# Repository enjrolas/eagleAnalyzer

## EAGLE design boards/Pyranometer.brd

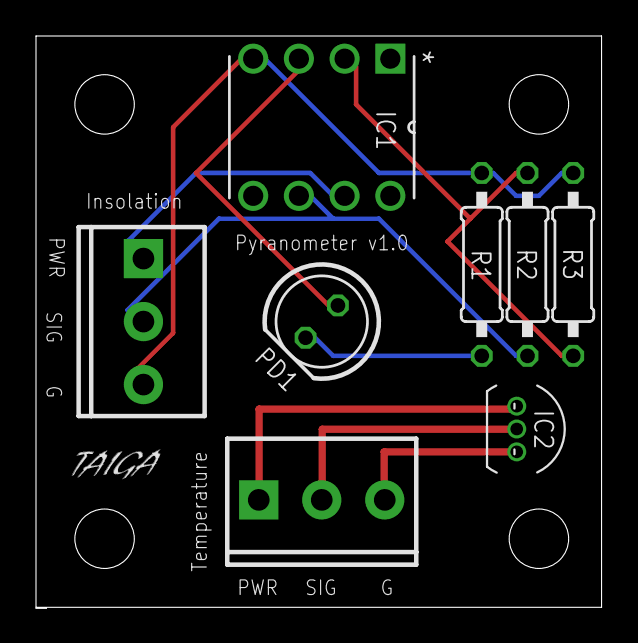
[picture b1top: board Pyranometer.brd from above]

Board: 2 copper layers, 31.4 x 31.7 mm, 12 parts (0 on the bottom side), 9 nets.

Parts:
IC1: LTC1050CN8PBF; DIP254P762X508-8
IC2: LM35; TO92-OVAL
JP1, JP2, JP3, JP4: STAND-OFF
PD1: LED5MM
R1, R2, R3: 0207/10
U$1, U$2: SCREWTERM3-3P5; SCREWTERM3P5-3

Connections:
5V: IC1.7, U$1.P1-1
GND: IC1.4, R1.2, R3.2, U$1.P1-3
unnamed: PD1.K, R1.1
unnamed: IC1.3, PD1.A
unnamed: IC1.2, R2.1, R3.1
unnamed: IC2.1, U$2.P1-1
unnamed: IC2.3, U$2.P1-3
unnamed: IC2.2, U$2.P1-2
SIG: IC1.6, R2.2, U$1.P1-2

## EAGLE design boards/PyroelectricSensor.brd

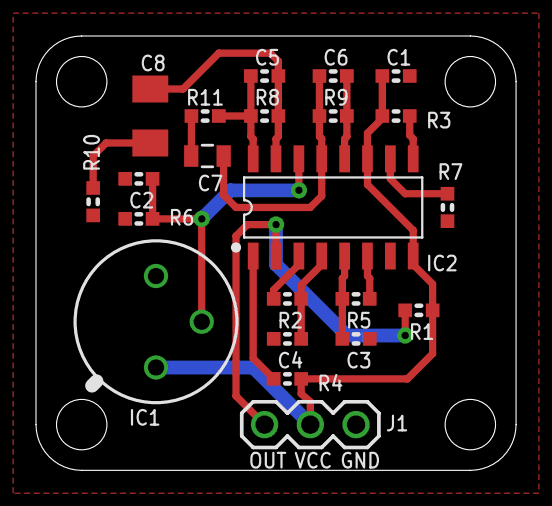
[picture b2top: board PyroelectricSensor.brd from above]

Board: 2 copper layers, 26.7 x 24.1 mm, 23 parts (1 on the bottom side), 17 nets.

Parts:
C1: 100nF; 0603
C2, C3, C4, C5, C6: 10nF; 0603
C7: 10µF; 0805
C8: 47µF; C1206K
IC1: RE200B; TO5-CAN
IC2: BIS0001; 16-SOIC
J1: 1X03
R1, R2, R3, R4, R11: 10kΩ; 0603
R5: 15kΩ; 0603
R6, R10: 47kΩ; 0603
R7, R9: 1MΩ; 0603
R8: 2MΩ; 0603
SY: OSHW-LOGOS; OSHW-LOGO-S

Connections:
+3V3: C1.1, IC1.1, IC2.8, IC2.11, J1.2, R1.2, R3.2, R4.2
GND: C1.2, C2.2, C3.2, C4.2, IC1.3, IC2.7, J1.3, R6.1, R7.1, R10.2
unnamed: IC2.6, R5.2
unnamed: IC2.10, R7.2
unnamed: C5.1, C8.2, IC2.15, R8.2
unnamed: IC2.2, J1.1, R1.1
unnamed: IC2.1, R4.1
unnamed: IC2.3, R2.2
unnamed: C4.1, IC2.4, R2.1
unnamed: C3.1, IC2.5, R5.1
unnamed: IC2.9, R3.1
unnamed: C2.1, IC1.2, IC2.14, R6.2
unnamed: C6.1, C7.2, IC2.13, R9.2
unnamed: C6.2, IC2.12, R9.1
unnamed: C5.2, IC2.16, R8.1, R11.2
unnamed: C7.1, R11.1
unnamed: C8.1, R10.1

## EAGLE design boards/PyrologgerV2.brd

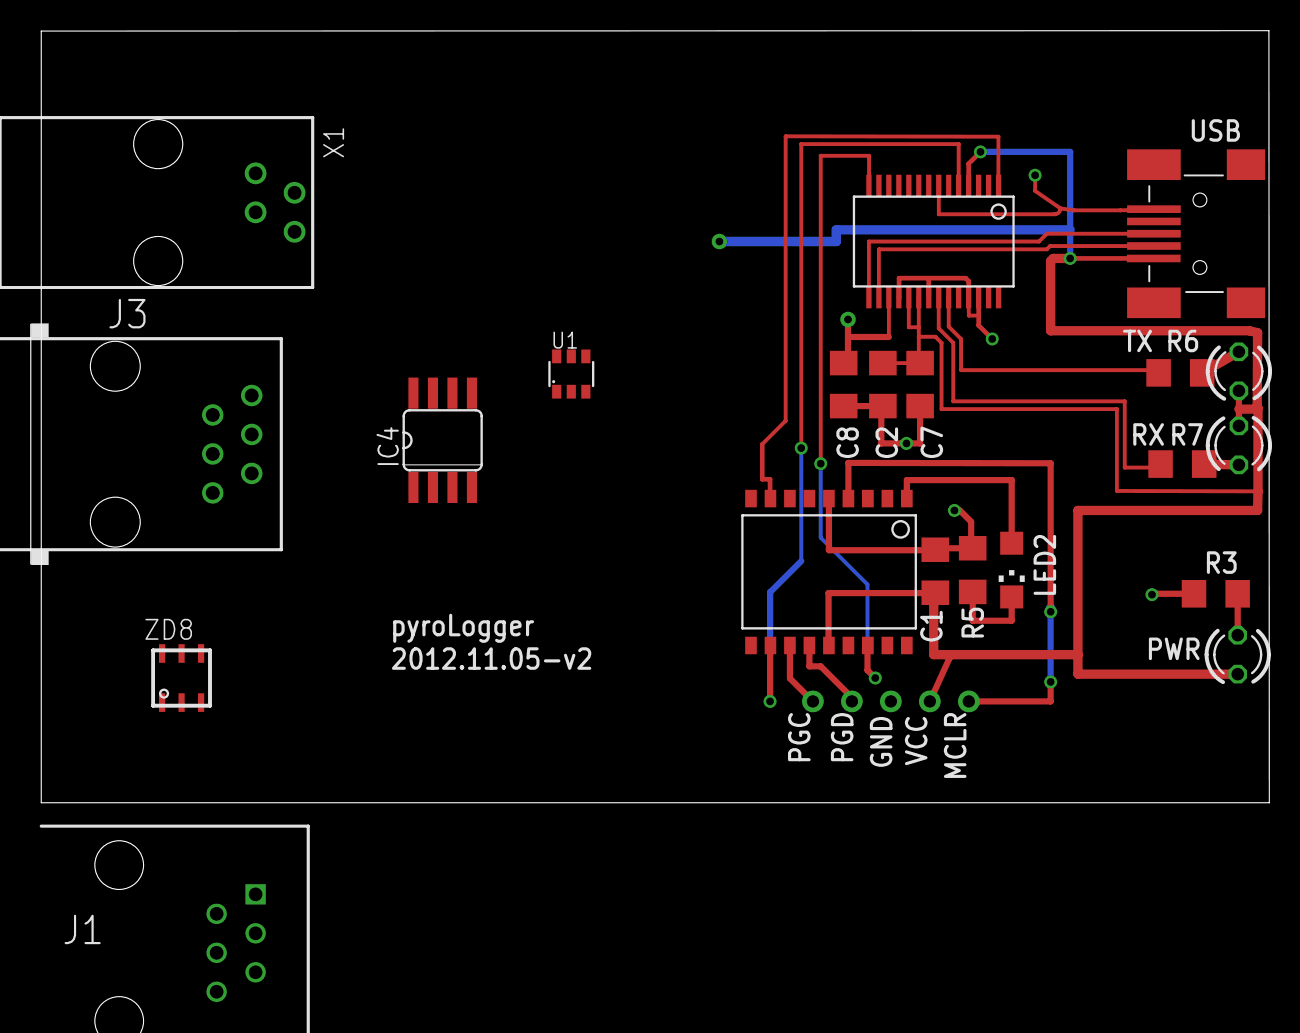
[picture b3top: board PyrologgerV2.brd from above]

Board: 2 copper layers, 80.7 x 50.3 mm, 26 parts (0 on the bottom side), 18 nets.

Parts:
C1, C8: .1uF; C1206@1
C2: 4.7uF; C1206@1
C7: .01uF; C1206@1
IC1: 16F88; SO-18W
IC2: FT232RL; SSOP28DB
IC4: DS2482-100S; SO08
J1: CONN-RJ11
J3: RJ11-2L-B; RJ11-NO_SHIELD
LED1, LED3, LED4: LED3MM
LED2: CHIPLED_1206
R3, R5, R6, R7: 330; R1206
TP1, TP2, TP5, TP6, TP7: PTR1PAD1-13; P1-13@1
U1: DS2483; TSOT23
X1: 14867
X4: USBMINIB; USB-MINIB
ZD8: DS9503P; TSOC6

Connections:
3.3V: C8.1, IC2.17
+5V: C1.1, C2.1, C7.1, IC1.14, IC2.4, IC2.19, IC2.20, LED1.A, LED3.A, LED4.A, TP6.TP, X4.VBUS
GND: C1.2, C2.2, C7.2, C8.2, IC1.5, IC2.7, IC2.18, IC2.21, IC2.25, IC2.26, IC4.3, J1.5, R3.1, R5.2, TP5.TP, U1.4, X4.GND
MCLR: IC1.4, TP7.TP
unnamed: IC2.15, X4.D+
unnamed: IC2.16, X4.D-
unnamed: LED3.K, R6.2
unnamed: LED4.K, R7.2
unnamed: IC2.23, R6.1
unnamed: IC2.22, R7.1
unnamed: LED1.K, R3.2
unnamed: IC1.1, LED2.A
unnamed: LED2.C, R5.1
OSC: IC1.16, IC2.14
PGC: IC1.13, TP1.TP
PGD: IC1.12, TP2.TP
RX: IC1.8, IC2.1
TX: IC1.11, IC2.5

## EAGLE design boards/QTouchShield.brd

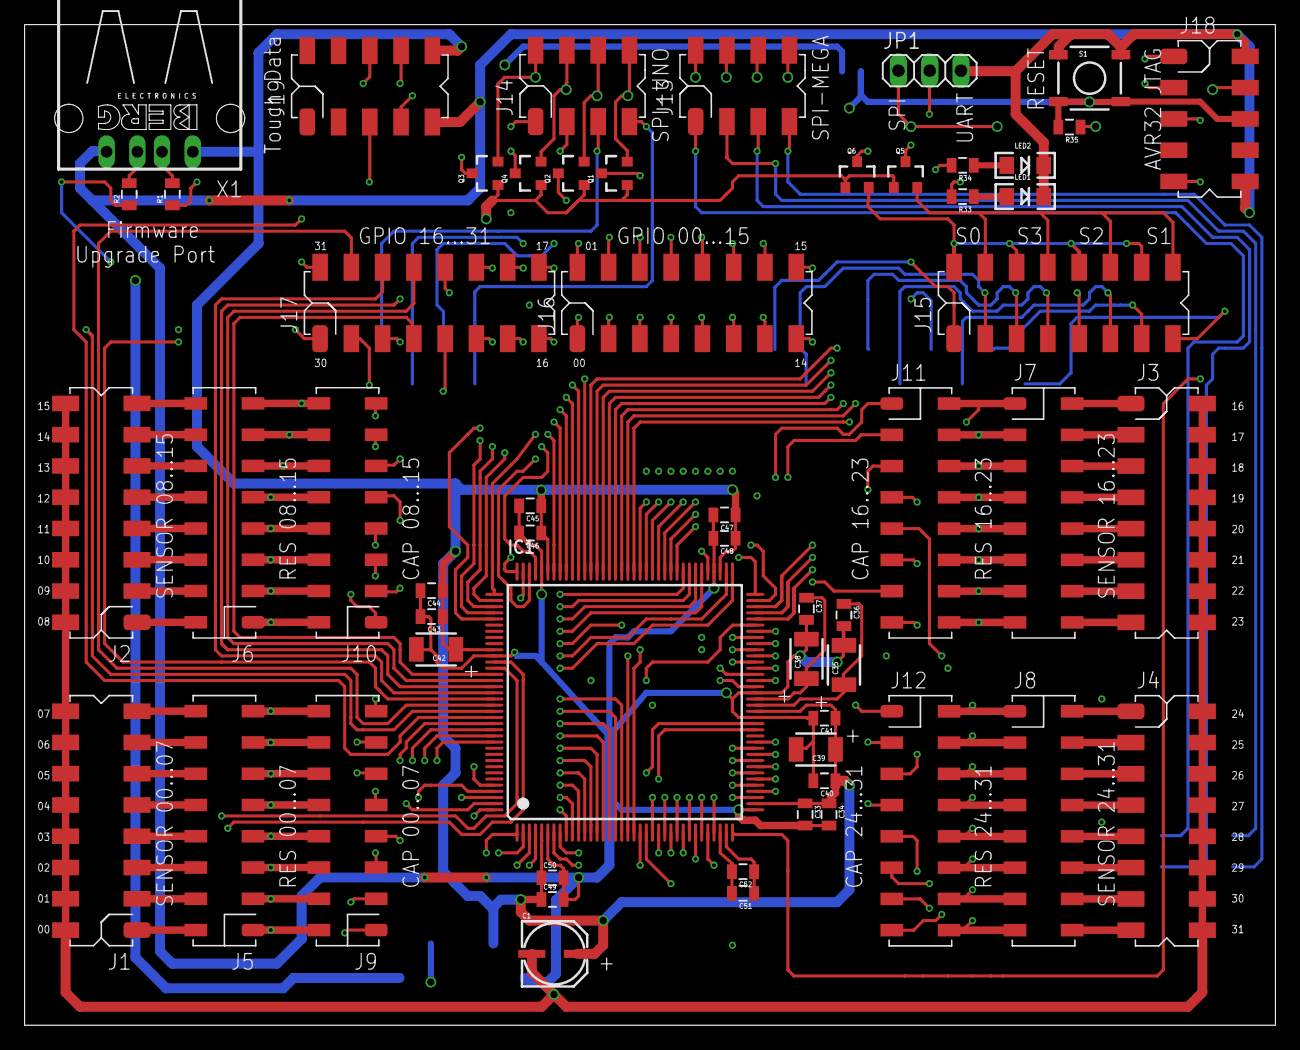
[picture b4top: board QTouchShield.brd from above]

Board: 4 copper layers, 101.6 x 81.3 mm, 59 parts (1 on the bottom side), 182 nets.

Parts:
C1: 10uF/35V; PANASONIC_C
C33, C40, C43, C45, C47, C49, C51: 100nF; 0805
C34, C41, C44, C46, C48, C50, C52: 33nF; 0805
C35, C38: 2.2uF; 1210
C36, C37: 470pF; 0805
C39, C42: 4.7uF; 1210
IC1: AT32UC3C0512CJEDEC-MS-026; LQFP144
J1: SENSOR 00...07; 2X8-V-MALE-SMT-HARWIN
J2: SENSOR 08...15; 2X8-V-MALE-SMT-HARWIN
J3: SENSOR 16...23; 2X8-V-MALE-SMT-HARWIN
J4: SENSOR 24...31; 2X8-V-MALE-SMT-HARWIN
J5: RES 00...07; 2X8-V-FEMALE-SMT-HARWIN
J6: RES 08...15; 2X8-V-FEMALE-SMT-HARWIN
J7: RES 16...23; 2X8-V-FEMALE-SMT-HARWIN
J8: RES 24...31; 2X8-V-FEMALE-SMT-HARWIN
J9: CAP 00...07; 2X8-V-FEMALE-SMT-HARWIN
J10: CAP 08...15; 2X8-V-FEMALE-SMT-HARWIN
J11: CAP 16...23; 2X8-V-FEMALE-SMT-HARWIN
J12: CAP 24...31; 2X8-V-FEMALE-SMT-HARWIN
J13: SPI-MEGA; 2X4-V-MALE-SMT-HARWIN
J14: SPI-UNO; 2X4-V-MALE-SMT-HARWIN
J15: COMMS Select; 2X8-V-MALE-SMT-HARWIN
J16: DETECT00...15; 2X8-V-MALE-SMT-HARWIN
J17: DETECT16...31; 2X8-V-MALE-SMT-HARWIN
J18: JTAG; 2X5-V-MALE-SMT-HARWIN
J19: TOUCH DATA; 2X5-V-MALE-SMT-HARWIN
JP1: COMMS_SELECT; 1X03
LED1: Yellow; LED-1206
LED2: Green; LED-1206
Q1, Q2, Q3, Q4, Q5, Q6: BSS138; SOT23-3
R1, R2: 39R; 0805
R33, R34: 470Ohm; 0805
R35: 10K; 0805
S1: RESET; TACTILE_SWITCH_SMD
SJ5: RESET-LINK; SJ
U1: ARDUINO-2560-MEGA-R3-SMD; ARDUINO-2560-R3-SMD
X1: Firmware Upgrade Port; PN87520

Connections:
ADCVREFN: C51.1, C52.1, IC1.35
ADCVREFP: C51.2, C52.2, IC1.34
ADT-SPI0-MISO: J13.2, J14.2, Q3.2
ADT-SPI0-MOSI: J13.4, J14.4, Q4.2
ADT-SPI0-SCK: J13.6, J14.6, Q2.2
ADT-SPI0-SS: J13.8, J14.8, Q1.2
ADT-USART0-RXD: J15.4, J15.8, J15.12, J15.16, Q5.2
ADT-USART0-TXD: J15.2, J15.6, J15.10, J15.14, Q6.2
ARDUINO_RESET: SJ5.1, U1.RESET
GND: C1.-, C33.2, C34.2, C35.2, C36.2, C37.2, C38.2, C39.2, C40.2, C41.2, C42.2, C43.2, C44.2, C45.2, C46.2, C47.2, C48.2, C49.2, C50.2, IC1.6, IC1.37, IC1.52, IC1.56, IC1.76, IC1.104, IC1.119, J1.2, J1.4, J1.6, J1.8, J1.10, J1.12, J1.14, J1.16, J2.2, J2.4, J2.6, J2.8, J2.10, J2.12, J2.14, J2.16, J3.2, J3.4, J3.6, J3.8, J3.10, J3.12, J3.14, J3.16, J4.2, J4.4, J4.6, J4.8, J4.10, J4.12, J4.14, J4.16, J18.2, J18.10, J19.9, JP1.3, LED1.C, LED2.C, S1.1, S1.2, U1.GND_1, U1.GND_2, X1.4
IOREF: Q1.1, Q2.1, Q3.1, Q4.1, Q5.1, Q6.1, U1.IOREF
JTAG_RESET: IC1.142, J18.6, R35.2, S1.3, S1.4, SJ5.2
JTAG_TCK: IC1.1, J18.1
JTAG_TDI: IC1.2, J18.9
JTAG_TDO: IC1.3, J18.3
JTAG_TMS: IC1.4, J18.5
MISO-MEGA: J13.1, U1.50
MISO-UNO: J14.1, U1.PWM12
MOSI-MEGA: J13.3, U1.51
MOSI-UNO: J14.3, U1.PWM11
unnamed: LED1.A, R33.1
unnamed: J4.15, J8.16
unnamed: J4.13, J8.14
unnamed: J4.11, J8.12
unnamed: J4.9, J8.10
unnamed: J4.7, J8.8
unnamed: J4.5, J8.6
unnamed: J4.3, J8.4
unnamed: J4.1, J8.2
unnamed: J3.15, J7.16
unnamed: J3.13, J7.14
unnamed: J3.11, J7.12
unnamed: J3.9, J7.10
unnamed: J3.7, J7.8
unnamed: J3.5, J7.6
unnamed: J3.3, J7.4
unnamed: J3.1, J7.2
unnamed: J2.15, J6.16
unnamed: J2.13, J6.14
unnamed: J2.11, J6.12
unnamed: J2.9, J6.10
unnamed: J2.7, J6.8
unnamed: J2.5, J6.6
unnamed: J2.3, J6.4
unnamed: J2.1, J6.2
unnamed: J1.15, J5.16
unnamed: J1.13, J5.14
unnamed: J1.11, J5.12
unnamed: J1.9, J5.10
unnamed: J1.7, J5.8
unnamed: J1.5, J5.6
unnamed: J1.3, J5.4
unnamed: J1.1, J5.2
unnamed: R1.2, X1.2
unnamed: R2.2, X1.3
unnamed: LED2.A, R34.1
QT-DETECT-GENERAL: IC1.21, R33.2
RX0: J15.3, U1.RX_PWM00
RX1: J15.15, U1.RX1_19
RX2: J15.11, U1.RX2_17
RX3: J15.7, U1.RX3_15
SCK-MEGA: J13.5, U1.52
SCK-UNO: J14.5, U1.PWM13
SDT-SPI0-MISO: IC1.112, Q3.3
SDT-SPI0-MOSI: IC1.111, Q4.3
SDT-SPI0-SCK: IC1.113, Q2.3
SDT-SPI0-SS: IC1.110, Q1.3
SDT-USART0-RXD: IC1.108, Q6.3
SDT-USART0-TXD: IC1.107, Q5.3
SHIELD-DATA-TRANSFER-COM-SELECT: IC1.109, JP1.2
SHIELD-DATA-TRANSFER-VISUAL-OUTPUT: IC1.22, R34.2
SHIELD-DETECT0: IC1.23, J16.1
SHIELD-DETECT1: IC1.24, J16.2
SHIELD-DETECT2: IC1.25, J16.3
SHIELD-DETECT3: IC1.26, J16.4
SHIELD-DETECT4: IC1.27, J16.5
SHIELD-DETECT5: IC1.28, J16.6
SHIELD-DETECT6: IC1.29, J16.7
SHIELD-DETECT7: IC1.30, J16.8
SHIELD-DETECT8: IC1.31, J16.9
SHIELD-DETECT9: IC1.32, J16.10
SHIELD-DETECT10: IC1.33, J16.11
SHIELD-DETECT11: IC1.36, J16.12
SHIELD-DETECT12: IC1.39, J16.13
SHIELD-DETECT13: IC1.40, J16.14
SHIELD-DETECT14: IC1.41, J16.15
SHIELD-DETECT15: IC1.42, J16.16
SHIELD-DETECT16: IC1.43, J17.15
SHIELD-DETECT17: IC1.44, J17.16
SHIELD-DETECT18: IC1.45, J17.13
SHIELD-DETECT19: IC1.46, J17.14
SHIELD-DETECT20: IC1.47, J17.11
SHIELD-DETECT21: IC1.48, J17.12
SHIELD-DETECT22: IC1.120, J17.9
SHIELD-DETECT23: IC1.121, J17.10
SHIELD-DETECT24: IC1.122, J17.7
SHIELD-DETECT25: IC1.123, J17.8
SHIELD-DETECT26: IC1.124, J17.5
SHIELD-DETECT27: IC1.125, J17.6
SHIELD-DETECT28: IC1.126, J17.3
SHIELD-DETECT29: IC1.127, J17.4
SHIELD-DETECT30: IC1.128, J17.1
SHIELD-DETECT31: IC1.129, J17.2
SNS0: IC1.140, J9.1
SNS1: IC1.141, J9.3
SNS2: IC1.143, J9.5
SNS3: IC1.144, J9.7
SNS4: IC1.7, J9.9
SNS5: IC1.8, J9.11
SNS6: IC1.9, J9.13
SNS7: IC1.10, J9.15
SNS8: IC1.11, J10.1
SNS9: IC1.12, J10.3
SNS10: IC1.13, J10.5
SNS11: IC1.14, J10.7
SNS12: IC1.15, J10.9
SNS13: IC1.16, J10.11
SNS14: IC1.17, J10.13
SNS15: IC1.18, J10.15
SNS16: IC1.19, J11.1
SNS17: IC1.20, J11.3
SNS18: IC1.57, J11.5
SNS19: IC1.58, J11.7
SNS20: IC1.59, J11.9
SNS21: IC1.60, J11.11
SNS22: IC1.61, J11.13
SNS23: IC1.62, J11.15
SNS24: IC1.63, J12.1
SNS25: IC1.64, J12.3
SNS26: IC1.65, J12.5
SNS27: IC1.66, J12.7
SNS28: IC1.67, J12.9
SNS29: IC1.68, J12.11
SNS30: IC1.69, J12.13
SNS31: IC1.70, J12.15
SNSK0: IC1.71, J5.1, J9.2
SNSK1: IC1.72, J5.3, J9.4
SNSK2: IC1.73, J5.5, J9.6
SNSK3: IC1.74, J5.7, J9.8
SNSK4: IC1.77, J5.9, J9.10
SNSK5: IC1.78, J5.11, J9.12
SNSK6: IC1.79, J5.13, J9.14
SNSK7: IC1.80, J5.15, J9.16
SNSK8: IC1.81, J6.1, J10.2
SNSK9: IC1.82, J6.3, J10.4
SNSK10: IC1.83, J6.5, J10.6
SNSK11: IC1.84, J6.7, J10.8
SNSK12: IC1.85, J6.9, J10.10
SNSK13: IC1.86, J6.11, J10.12
SNSK14: IC1.87, J6.13, J10.14
SNSK15: IC1.88, J6.15, J10.16
SNSK16: IC1.89, J7.1, J11.2
SNSK17: IC1.90, J7.3, J11.4
SNSK18: IC1.91, J7.5, J11.6
SNSK19: IC1.92, J7.7, J11.8
SNSK20: IC1.93, J7.9, J11.10
SNSK21: IC1.94, J7.11, J11.12
SNSK22: IC1.95, J7.13, J11.14
SNSK23: IC1.96, J7.15, J11.16
SNSK24: IC1.97, J8.1, J12.2
SNSK25: IC1.98, J8.3, J12.4
SNSK26: IC1.99, J8.5, J12.6
SNSK27: IC1.100, J8.7, J12.8
SNSK28: IC1.101, J8.9, J12.10
SNSK29: IC1.102, J8.11, J12.12
SNSK30: IC1.105, J8.13, J12.14
SNSK31: IC1.106, J8.15, J12.16
SS-MEGA: J13.7, U1.53
SS-UNO: J14.7, U1.PWM10
TOUCH_DATA-MISO: IC1.133, J19.7
TOUCH_DATA-MOSI: IC1.132, J19.6
TOUCH_DATA-SCK: IC1.131, J19.8
TOUCH_DATA-SS: IC1.130, J19.5
TX0: J15.1, U1.TX_PWM01
TX1: J15.13, U1.TX1_18
TX2: J15.9, U1.TX2_16
TX3: J15.5, U1.TX3_14
USB-DM: IC1.50, R1.1
USB-DP: IC1.51, R2.1
VCC: C1.+, C33.1, C34.1, C39.1, C40.1, C41.1, C42.1, C43.1, C44.1, C45.1, C46.1, C47.1, C48.1, C49.1, C50.1, IC1.5, IC1.38, IC1.53, IC1.75, IC1.103, IC1.118, J18.4, J19.10, JP1.1, R35.1, U1.5V_1, X1.1
VDDCORE: C37.1, C38.1, IC1.55
VDDIN_33: C35.1, C36.1, IC1.54

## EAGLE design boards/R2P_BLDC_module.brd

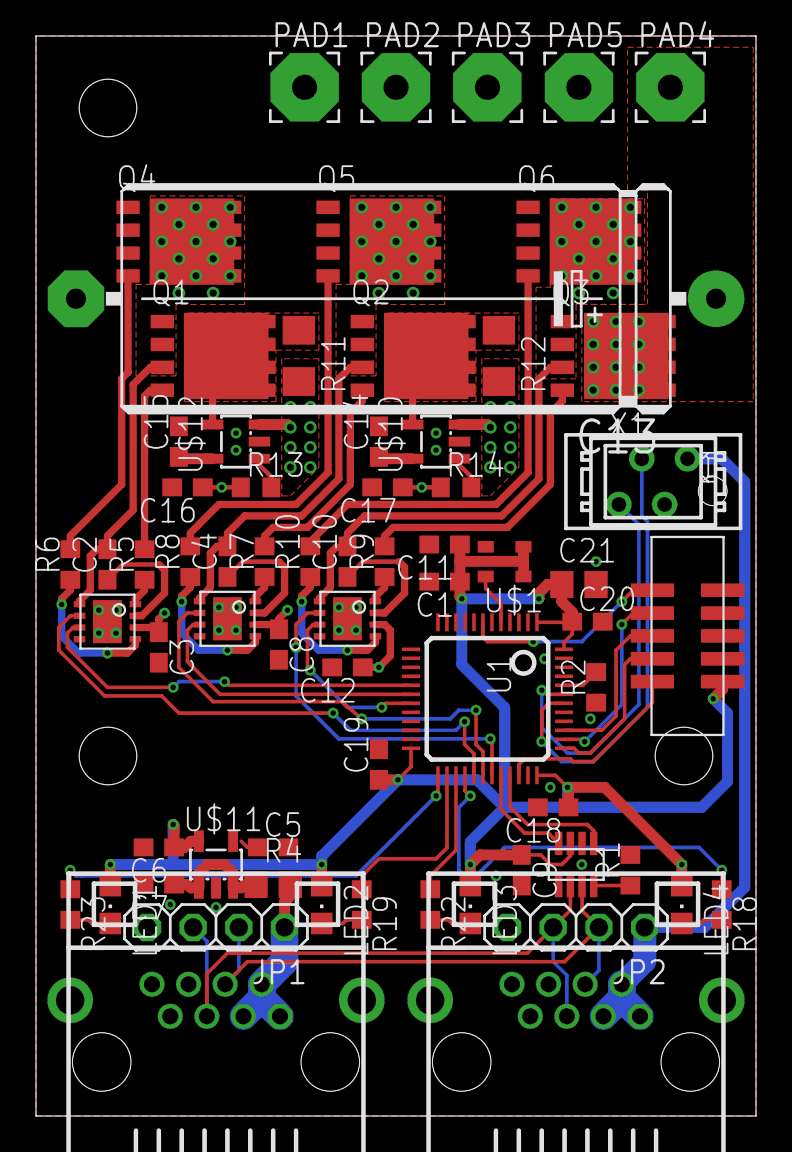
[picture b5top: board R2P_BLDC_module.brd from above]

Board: 2 copper layers, 40.0 x 60.0 mm, 68 parts (0 on the bottom side), 59 nets.

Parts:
1, 2: RJ45-43860; 0438600010
C1, C9, C14, C15, C16, C17, C18, C19, C20: 100n; C0603
C2, C4, C10, C11: 15pF; C0603
C3, C8, C12: 470nF; C0603
C5: 10n; C0603
C6, C7: 1u; C0603
C13: E35-12
C21: 4.7u; C0805
JP1, JP2: 1X04
LED1, LED2, LED3, LED4: CHIPLED_0805
PAD1, PAD2, PAD3, PAD4, PAD5: 3,81/1,4
Q1, Q2, Q3, Q4, Q5, Q6: OPTIMOS; PG-TDSON-8
R1: 0; R0603
R2: 10k; R0603
R4: PTC; R0805
R5, R6, R7, R8, R9, R10, R13, R14: 10; R0603
R11, R12: R1206
R18, R19, R22, R23: 330; R0603
SOT1: MAX3051; SOT23-8L
U1: STM32F103CX; LQFP48
U$1: ASE
U$2, U$8, U$9: MCP14700MF; DFN8
U$4: FTSH-105
U$10, U$12: INA193DBV; SOT23-5L
U$11: TPS73033; SOT23-5L
X1: MICROMATCH-4

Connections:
+3V3: C1.1, C6.1, C9.1, C11.1, C18.1, C19.1, C20.1, C21.1, LED1.A, LED2.A, LED3.A, LED4.A, SOT1.P$3, U1.1, U1.24, U1.36, U1.48, U$1.1, U$1.4, U$4.P$1, U$11.5
+5V: C3.1, C7.1, C8.1, C12.1, R4.1, U$2.P$6, U$8.P$6, U$9.P$6, U$11.1, U$11.3
+A3V3: C14.1, C15.1, U1.9, U$10.5, U$12.5
+V: C13.+, PAD4.1, Q3.5, Q3.6, Q3.7, Q3.8, Q3.TH, R11.2, R12.2, U$10.3, U$12.3
+VBUS: 1.P$1, 1.P$2, 1.P$3, 2.P$1, 2.P$2, 2.P$3, JP1.1, JP2.1, R4.2, X1.1
AH: U1.29, U$2.P$2
AL: U1.17, U$2.P$3
BH: U1.30, U$8.P$2
BL: U1.18, U$8.P$3
BOOT0: R2.2, U1.44
CANH: 1.P$4, 2.P$4, JP1.2, JP2.2, SOT1.P$7
CANL: 1.P$5, 2.P$5, JP1.3, JP2.3, SOT1.P$6
CAN_RX: SOT1.P$4, U1.32
CAN_TX: SOT1.P$1, U1.33
CH: U1.31, U$9.P$2
CL: U1.19, U$9.P$3
GAH: R5.1, U$2.P$8
GAL: R6.1, U$2.P$5
GBH: R7.1, U$8.P$8
GBL: R8.1, U$8.P$5
GCH: R9.1, U$9.P$8
GCL: R10.1, U$9.P$5
GND: 1.P$6, 1.P$7, 1.P$8, 1.P$9, 1.P$10, 2.P$6, 2.P$7, 2.P$8, 2.P$9, 2.P$10, C1.2, C3.2, C5.2, C6.2, C7.2, C8.2, C9.2, C11.2, C12.2, C13.-, C14.2, C15.2, C16.2, C17.2, C18.2, C19.2, C20.2, C21.2, JP1.4, JP2.4, PAD5.1, Q4.1, Q4.2, Q4.3, Q5.1, Q5.2, Q5.3, Q6.1, Q6.2, Q6.3, R1.2, R2.1, SOT1.P$2, U1.8, U1.23, U1.35, U1.47, U$1.2, U$2.P$4, U$2.P$9, U$4.P$3, U$4.P$9, U$8.P$4, U$8.P$9, U$9.P$4, U$9.P$9, U$10.2, U$11.2, U$12.2, X1.2
IA: C16.1, R13.1
IB: C17.1, R14.1
JTCK: U1.37, U$4.P$4
JTDI: U1.38, U$4.P$8
JTDO: U1.39, U$4.P$6
JTMS: U1.34, U$4.P$2
LED1: R23.1, U1.25
LED2: R19.1, U1.26
LED3: R22.1, U1.27
LED4: R18.1, U1.28
MA: C2.2, PAD1.1, Q1.1, Q1.2, Q1.3, Q4.5, Q4.6, Q4.7, Q4.8, Q4.TH, U$2.P$1
MB: C4.2, PAD2.1, Q2.1, Q2.2, Q2.3, Q5.5, Q5.6, Q5.7, Q5.8, Q5.TH, U$8.P$1
MC: C10.2, PAD3.1, Q3.1, Q3.2, Q3.3, Q6.5, Q6.6, Q6.7, Q6.8, Q6.TH, U$9.P$1
unnamed: R1.1, SOT1.P$8
unnamed: C5.1, U$11.4
unnamed: C4.1, U$8.P$7
unnamed: C2.1, U$2.P$7
unnamed: Q1.4, R5.2
unnamed: Q4.4, R6.2
unnamed: Q2.4, R7.2
unnamed: C10.1, U$9.P$7
unnamed: Q5.4, R8.2
unnamed: Q3.4, R9.2
unnamed: Q6.4, R10.2
unnamed: Q1.5, Q1.6, Q1.7, Q1.8, Q1.TH, R11.1, U$12.4
unnamed: LED4.C, R18.2
unnamed: Q2.5, Q2.6, Q2.7, Q2.8, Q2.TH, R12.1, U$10.4
unnamed: R13.2, U$12.1
unnamed: LED2.C, R19.2
unnamed: R14.2, U$10.1
unnamed: LED3.C, R22.2
unnamed: LED1.C, R23.2
NRST: U1.7, U$4.P$10
OSC_IN: U1.5, U$1.3
UART_RX: U1.43, X1.4
UART_TX: U1.42, X1.3

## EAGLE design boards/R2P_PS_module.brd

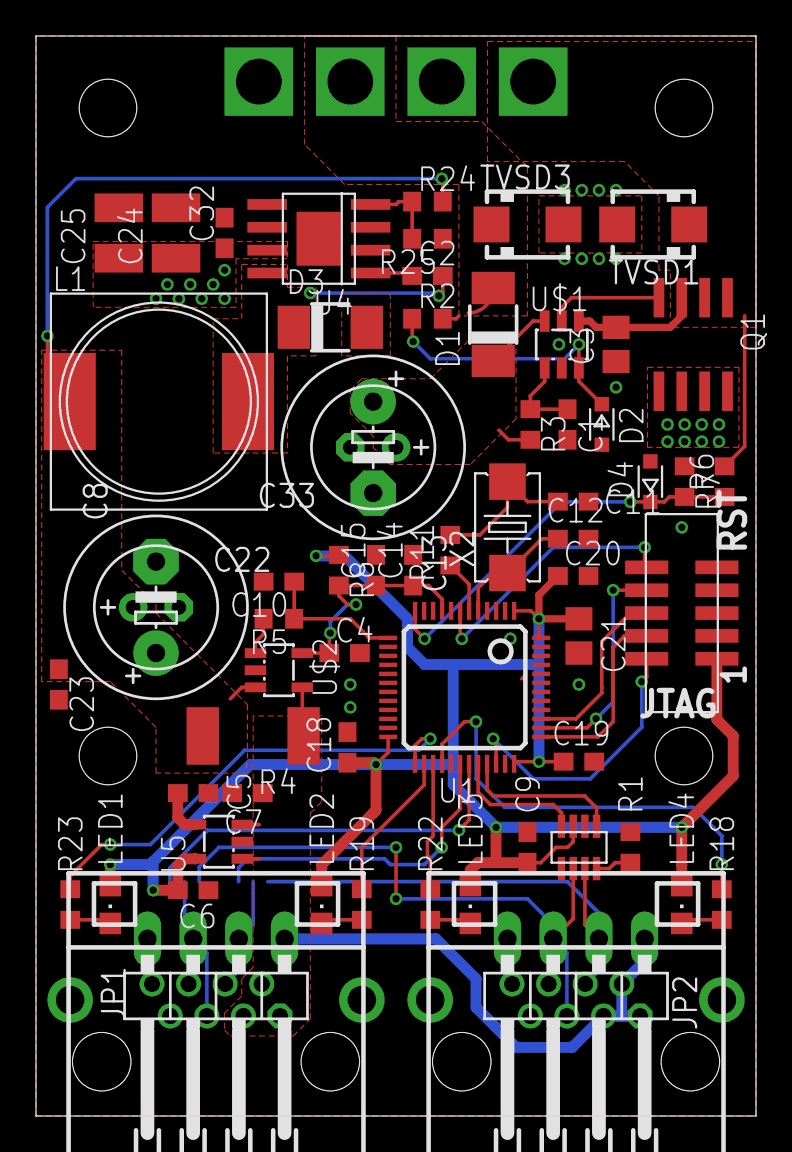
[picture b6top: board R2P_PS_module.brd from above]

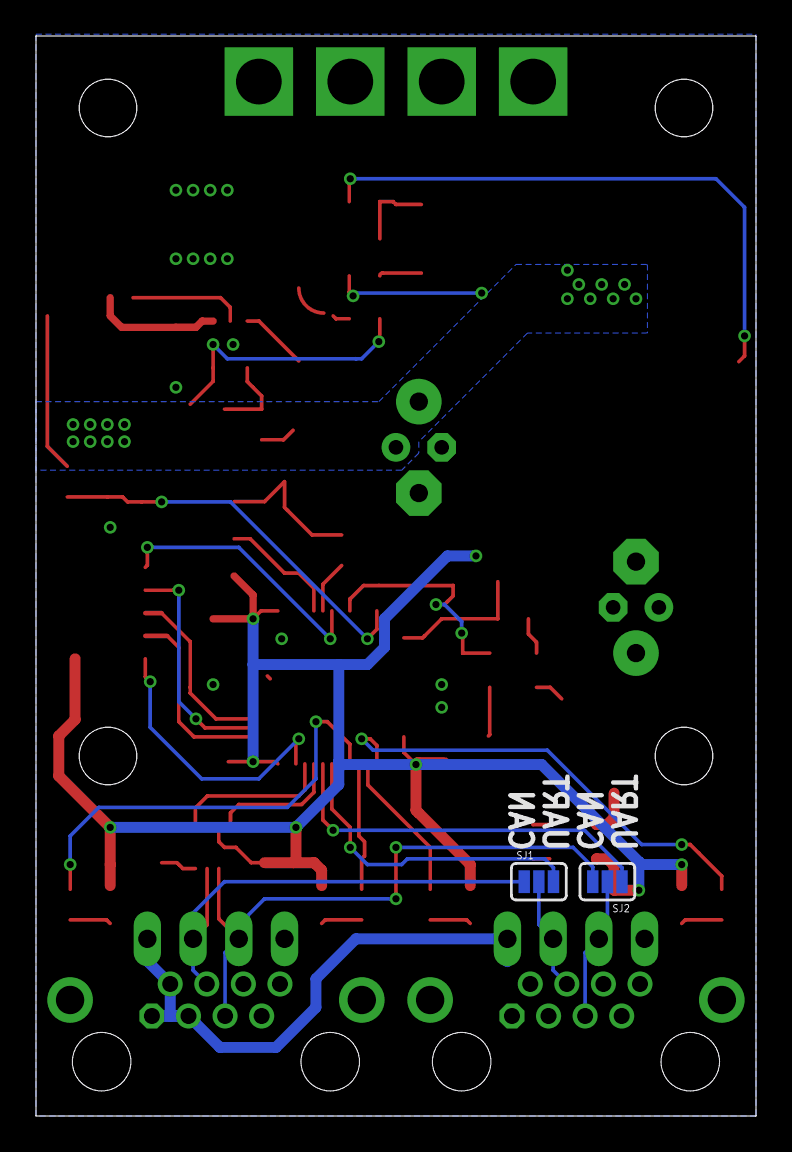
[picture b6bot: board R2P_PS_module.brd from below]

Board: 2 copper layers, 40.0 x 60.0 mm, 67 parts (2 on the bottom side), 43 nets.

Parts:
1, 2: RJ45-43860; 0438600010
C1, C32: 10nF; C0603
C2, C23: 10nF X5R; C0603
C3: C0805
C4, C9, C10, C14, C18, C19, C20: 100n; C0603
C5: 10n; C0603
C6, C7, C15: 1u; C0603
C8: E5-10,5
C11, C12: 15pF; C0603
C13: 100uF 50V; E5-10,5
C21: 4.7u; C0805
C22: 330uF 10V; E2,5-7
C24, C25: 4.7uF X5R; C1210
C33: 100uF 50V; E2,5-7
D1, D3: DO-214AC
D2, D4: SOD-323F
JP1, JP2: 1X04/90
L1: 15uH; CDRH127
LED1, LED2, LED3, LED4: CHIPLED_0805
Q1: SO-08
R1: 0; R0603
R2, R3: R0603
R4: R2512
R5, R25: 3k24; R0603
R6, R24: 10k; R0603
R7, R11: 1k; R0603
R8: RBEAD; R0603
R18, R19, R22, R23: 330; R0603
SJ1, SJ2: SJ_3_PASTE1&2
SOT1: MAX3051; SOT23-8L@1
TVSD1, TVSD3: SMAJ24A; SMA
U1: STM32F103CX; LQFP48
U4: TPS5450; POWERPAD-SO8
U5: LD3985XX; SOT23-5L
U$1: LM5050-1; SOT23-6L
U$2: INA193DBV; SOT23-5L
U$3: POWERCONN-4
U$4: FTSH-105
X2: OSC-XTAL212M_; 4X6

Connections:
+3V3: C6.1, C9.1, C18.1, C19.1, C20.1, C21.1, LED1.A, LED2.A, LED3.A, LED4.A, R8.1, SOT1.P$3, U1.1, U1.24, U1.36, U1.48, U5.5, U$4.P$1
+5V: 1.P$1, 1.P$2, 1.P$3, 2.P$1, 2.P$2, 2.P$3, C7.1, JP1.1, JP2.1, R4.1, U5.1, U5.3, U$2.4
+A3V3: C4.1, C14.1, C15.1, R8.2, U1.9, U$2.5
CANH: 2.P$4, JP2.2, SJ1.1, SOT1.P$7
CANL: 2.P$5, JP2.3, SJ2.3, SOT1.P$6
CAN_RX: SOT1.P$4, U1.32
CAN_TX: SOT1.P$1, U1.33
DCDC_OUT: C8.+, C22.+, C23.1, L1.P$2, R4.2, R24.2, U$2.3
GND: 1.P$6, 1.P$7, 1.P$8, 1.P$9, 1.P$10, 2.P$6, 2.P$7, 2.P$8, 2.P$9, 2.P$10, C1.2, C3.1, C4.2, C5.2, C6.2, C7.2, C8.-, C9.2, C10.2, C11.2, C12.2, C13.-, C14.2, C15.2, C18.2, C19.2, C20.2, C21.2, C22.-, C23.2, C24.2, C25.2, C32.2, C33.-, D2.A, D3.A, D4.A, JP1.4, JP2.4, R1.2, R7.1, R25.1, SOT1.P$2, TVSD1.A, TVSD3.A, U1.8, U1.23, U1.35, U1.44, U1.47, U4.P6, U4.PAD, U5.2, U$1.2, U$2.2, U$3.P$1, U$3.P$3, U$4.P$3, U$4.P$5, U$4.P$9
ISENSE: C10.1, R5.1, U1.13
JTCK: U1.37, U$4.P$4
JTDI: U1.38, U$4.P$8
JTDO: U1.39, U$4.P$6
JTMS: U1.34, U$4.P$2
LED1: R23.1, U1.25
LED2: R19.1, U1.26
LED3: R22.1, U1.27
LED4: R18.1, U1.28
unnamed: R1.1, SOT1.P$8
unnamed: 1.P$4, JP1.2, SJ1.2
unnamed: C5.1, U5.4
unnamed: D2.C, R2.1, U$1.3
unnamed: Q1.4, U$1.5
unnamed: 1.P$5, JP1.3, SJ2.2
unnamed: C1.1, R3.1, U$1.1
unnamed: C11.1, R11.1, X2.1
unnamed: R5.2, U$2.1
unnamed: LED4.C, R18.2
unnamed: LED2.C, R19.2
unnamed: LED3.C, R22.2
unnamed: LED1.C, R23.2
unnamed: C2.1, U4.P1
unnamed: R24.1, R25.2, U4.P4
NRST: U1.7, U$4.P$10
OSC_IN: C12.1, U1.5, X2.2
OSC_OUT: R11.2, U1.6
PH: C2.2, D3.C, L1.P$1, U4.P8
UART_RX: SJ2.1, U1.31
UART_TX: SJ1.3, U1.30
VBATT: C3.2, Q1.1, Q1.2, Q1.3, R6.2, TVSD1.C, U$1.4, U$3.P$4
VIN: C13.+, C24.1, C25.1, C32.1, C33.+, D1.C, Q1.5, Q1.6, Q1.7, Q1.8, R3.2, U4.P7, U$1.6
VPSU: D1.A, R2.2, TVSD3.C, U$3.P$2
VSENSE: D4.C, R6.1, R7.2, U1.12

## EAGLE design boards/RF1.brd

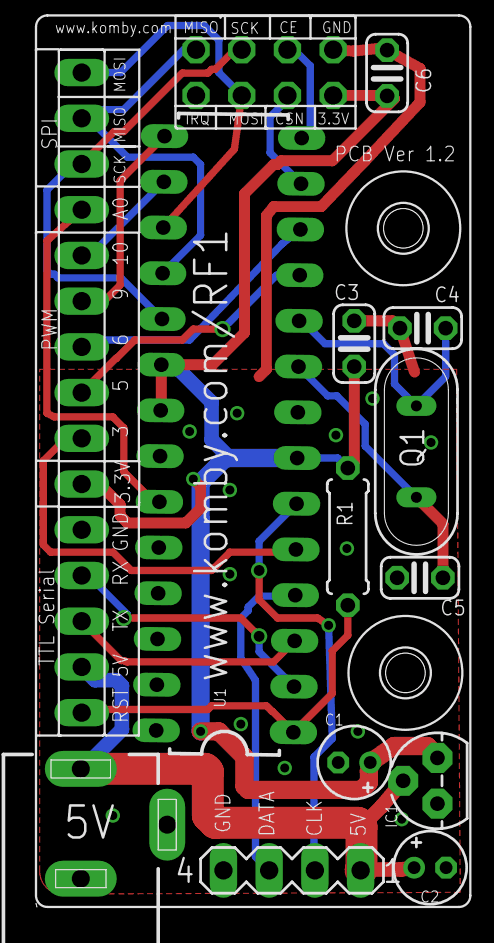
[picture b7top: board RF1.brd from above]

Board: 2 copper layers, 13 parts (0 on the bottom side), 21 nets.

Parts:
C1, C2: 10uf; E1,8-4
C3, C6: 100n; C025-024X044
C4, C5: 22pf; C025-024X044
IC1: TO92
J1: 5v; DCJ0303
Q1: 16mhz; QS
R1: 10k; 0207/7
SV1: MA04-1
U1: ATMEGA328P_PDIP; DIL28-3
U$3: RF1_5CMX2.5CM_SHEILD; KOMBY_RF1_SHEILD_5X2.5

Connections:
+3V3: C1.+, C3.1, C6.2, IC1.3, R1.2, U1.7, U1.20, U1.21, U$3.3.3V, U$3.RF_3.3V
+5V: C2.+, IC1.2, J1.1, SV1.1, U$3.5V
DATA: SV1.3, U1.4
GND: C1.-, C2.-, C3.2, C4.2, C5.2, C6.1, IC1.1, J1.2, J1.3, SV1.4, U1.8, U1.22, U$3.GND, U$3.RF_GND
MISO: U1.18, U$3.MISO, U$3.RF_MISO
MOSI: U1.17, U$3.MOSI, U$3.RF_MOSI
unnamed: C4.1, Q1.2, U1.10
unnamed: C5.1, Q1.1, U1.9
PC0: U1.23, U$3.A0
PCLK: SV1.2, U1.6
PWM1_D3: U1.5, U$3.PWM1_D3
PWM2_D5: U1.11, U$3.PWM2_D5
PWM3_D6: U1.12, U$3.PWM3_D6
PWM4_D9: U1.15, U$3.PWM4_D9
PWM5_D10: U1.16, U$3.PWM5_D10
RESET: R1.1, U1.1, U$3.RESET
RF_CE: U1.14, U$3.RF_CE
RF_CSN: U1.13, U$3.RF_CSN
RX: U1.2, U$3.RX
SCK: U1.19, U$3.RF_SCK, U$3.SCK
TX: U1.3, U$3.TX

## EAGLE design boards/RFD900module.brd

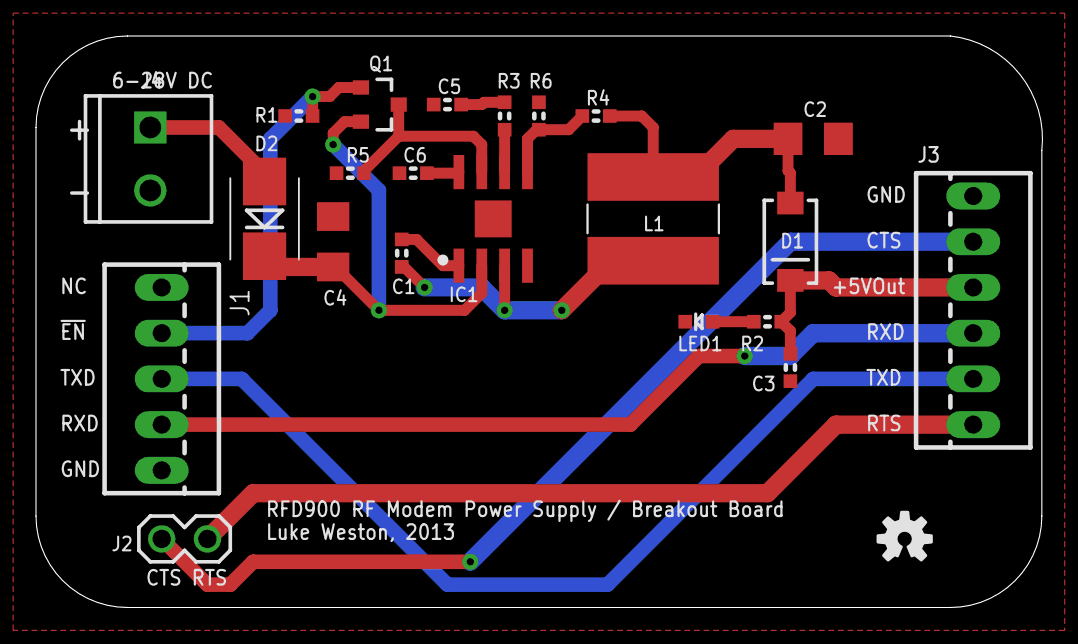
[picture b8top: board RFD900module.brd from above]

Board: 2 copper layers, 55.9 x 31.8 mm, 23 parts (0 on the bottom side), 18 nets.

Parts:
C1: 10nF; 0603
C2: 22uF; C1206
C3: 1µF; 0603
C4: 10uF; C1206
C5: 2.2nF; 0603
C6: 100nF; 0603
D1: SK34A-LTP; SMA-DIODE
D2: SS16; SMA-SMB-DIODE
IC1: EUP3476; SO08T
J1: Interface; 22-23-2051
J2: Flow; 1X02
J3: Output; 22-23-2061
J4: Power In; SCREWTERMINAL-3.5MM-2
L1: 6.8 uH; CDRH
LED1: Power; LED-0603
Q1: DMP2035U-7; SOT23-3
R1, R5: 10kΩ; 0603
R2: 1kΩ; 0603
R3: 15kΩ; 0603
R4: 53.6kΩ 1%; 0603
R6: 10kΩ 1%; 0603
SY: OSHW-LOGOS; OSHW-LOGO-S

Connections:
!ENABLE: J1.2, Q1.1, R1.1
+5V: C3.2, D1.C, J3.4, R2.1
CTS: J2.2, J3.5
GND: C2.2, C3.1, C4.2, C5.1, C6.1, IC1.4, IC1.9, J1.5, J3.6, J4.2, LED1.C, R1.2, R5.2, R6.2
unnamed: D2.A, J4.1
unnamed: IC1.7, Q1.3, R5.1
unnamed: LED1.A, R2.2
unnamed: C2.1, D1.A, L1.2, R4.2
unnamed: C1.1, IC1.3, L1.1
unnamed: C1.2, IC1.1
unnamed: C5.2, R3.2
unnamed: IC1.6, R3.1
unnamed: C6.2, IC1.8
unnamed: IC1.5, R4.1, R6.1
RTS: J2.1, J3.1
RXD: J1.4, J3.3
TXD: J1.3, J3.2
VIN: C4.1, D2.C, IC1.2, Q1.2

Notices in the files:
parts and their libraries:
SparkFun: Licensing: CC v3.0 Share-Alike You are welcome to use this library for commercial purposes.
